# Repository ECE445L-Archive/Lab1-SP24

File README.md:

# ECE445L-Lab1

ECE445L Lab 1 Spring 2024.

IMPORTANT (for those not using Github Classroom): To clone this repository,
click the green "Use this template" button and create a PRIVATE repository. Do
NOT clone this repository as you would normally clone a git repo (i.e. using
'git clone ...') because you will not be able to make a private fork.

## HW

The hw folder should contain your schematic and board files for your PCB or
circuits. In later labs, you will be creating schematics for your circuit
in EAGLE. A setup tutorial can be found
[here](https://www.shawnvictor.net/autodesk-eagle.html).

## SW

The sw folder should contain your application firmware and software written for
the lab. The sw/inc folder contains firmware drivers written for you by
Professor Valvano. Feel free to write your own (in fact, in some labs, you may
be required to write your own).

You can place any other source files in the sw/ folder. TAs will look at the
files you create and/or modify for software quality and for running your
project.

## Resources

A couple files are provided in the Resources folder so you don't have to keep
searching for that one TI document. Some of them are immediately useful, like
the TM4C datasheet. Others may be useful for your final project, like the
TM4C_System_Design_Guidelines page.

## Git and Github

We will extensively use Git and Github for managing lab projects. This makes it
easier for TAs to grade and help debug the project by allowing the students to
see commit histories, maintain a common project structure, collaborate with
partners, merge different codebases, and to debug work.

Two common ways of using Git and Github are [Github Desktop](https://desktop.github.com/) and the [command line](https://git-scm.com/downloads). [Tutorials](https://dev.to/mollynem/git-github--workflow-fundamentals-5496) are also abundant on the net for you to peruse. We've provided a cheatsheet for git in the Resources folder.

It is highly recommended to make the most out of Git, even if you've never used
it before. Version control will save you a lot of suffering, and tools like Git
or SVN are ubiquitous in the industry.

## Lab Report

Following the lab doc provided at the root of this project, the TAs request you
submit a lab report in Microsoft Word (or Pages, if you're a Mac user). Please
name it `EID_lab_LAB_NUMBER_report.pdf`.

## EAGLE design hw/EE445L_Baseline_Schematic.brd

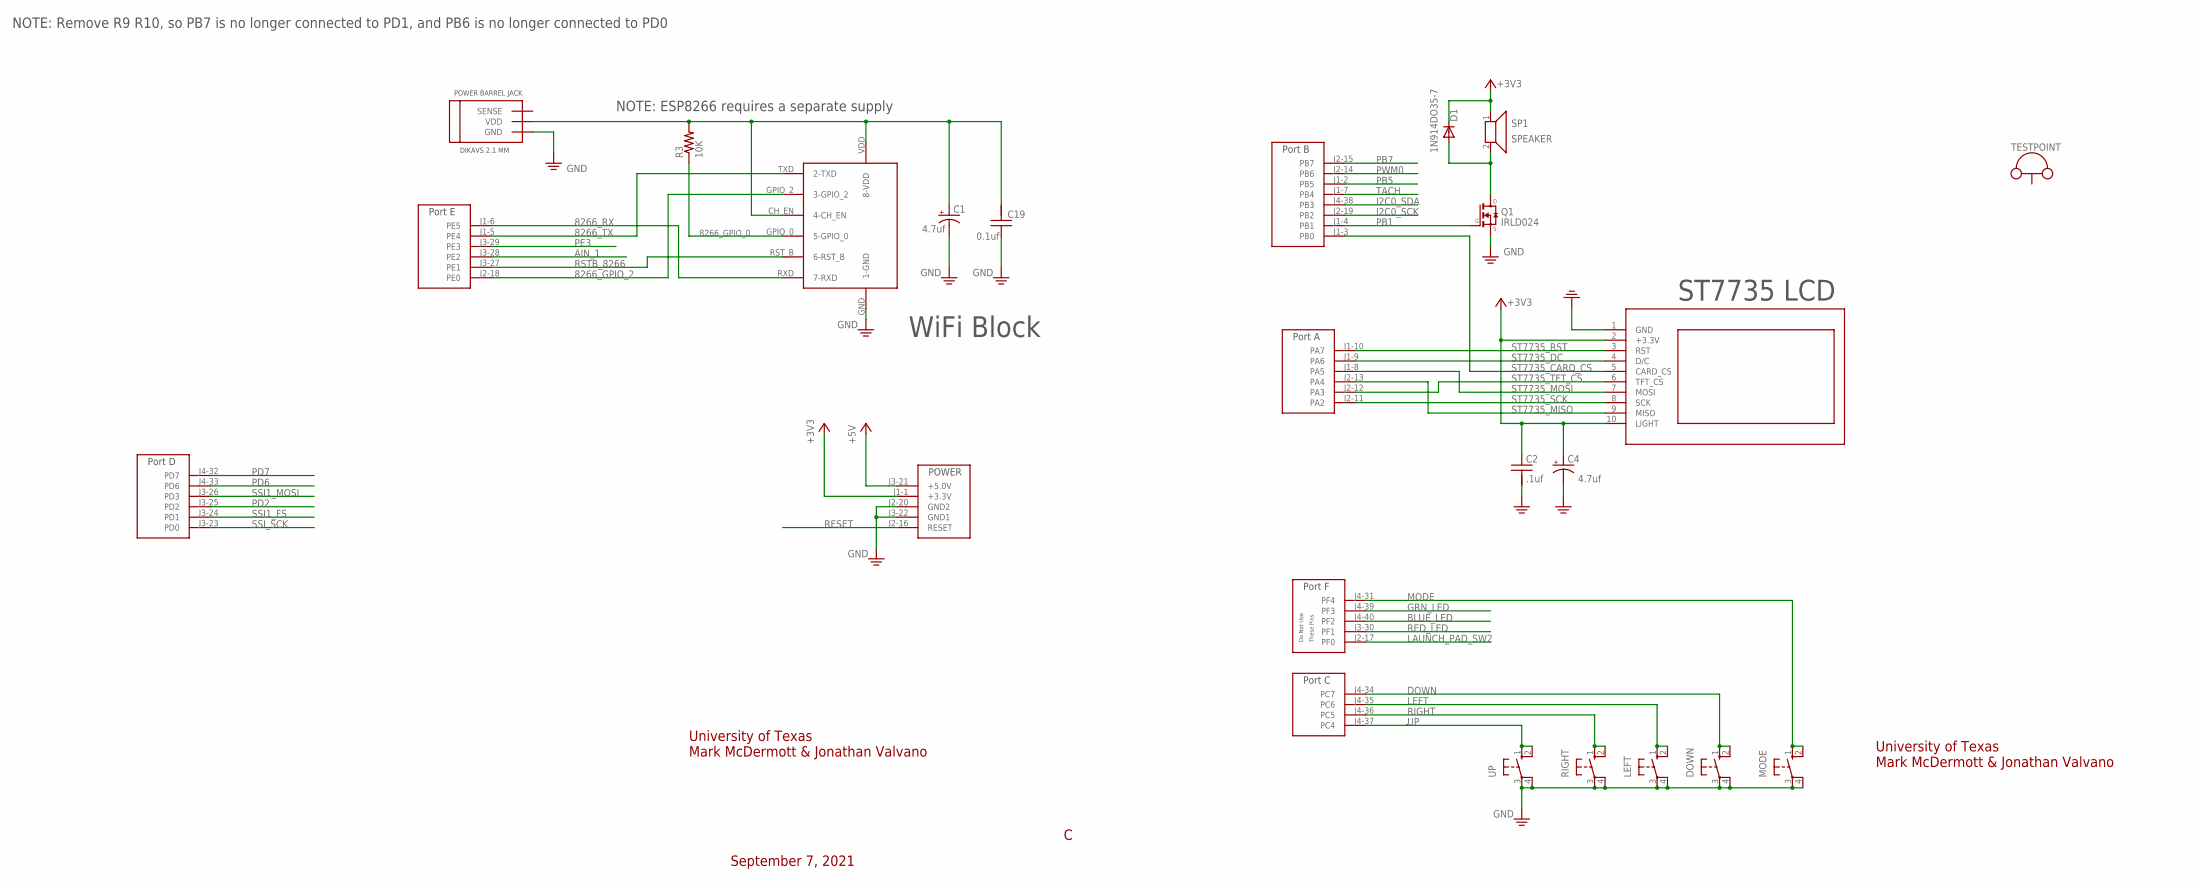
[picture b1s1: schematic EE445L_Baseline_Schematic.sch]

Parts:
C1, C4: 4.7uf; CAP200MILPOLARIZED
C2: .1uf; CAP200MIL
C19: 0.1uf; CAP200MIL
D1: 1N914DO35-7; DO35-7
DOWN: B3F-1052; B3F-10XX
LEFT: B3F-1052; B3F-10XX
MODE: B3F-1052; B3F-10XX
Q1: IRLD024
R3: 10K; RES300MIL
RIGHT: B3F-1052; B3F-10XX
SP1: SPEAKER; 1X02
TESTPOINT: TP_LOOP
U$1: ESP_8266; ESP8266
U$2: TM4C_BP; TM4C_BOOSTER_PACK
U$3: ST7735
U$4: 2.1MM_BARREL_JACK; 2.1M_BARREL_JACK
UP: B3F-1052; B3F-10XX

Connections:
8266_GPIO_0: R3.1, U$1.GPIO_0 (5-GPIO_0)
8266_GPIO_2: U$1.GPIO_2 (3-GPIO_2), U$2.J2-18 (PE0)
8266_RX: U$1.RXD (7-RXD), U$2.J1-6 (PE5)
8266_TX: U$1.TXD (2-TXD), U$2.J1-5 (PE4)
+3V3: C2.1, C4.+, D1.C, SP1.1, U$2.J1-1 (+3.3V), U$3.2 (+3.3V), U$3.10 (LIGHT)
+5V: U$2.J3-21 (+5.0V)
AIN_1: U$2.J3-28 (PE2)
BLUE_LED: U$2.J4-40 (PF2)
DOWN: DOWN.1 (S), DOWN.2 (S1), U$2.J4-34 (PC7)
GND: C1.-, C2.2, C4.-, C19.1, DOWN.3, DOWN.4 (P1), LEFT.3, LEFT.4 (P1), MODE.3, MODE.4 (P1), Q1.P$4 (S), RIGHT.3, RIGHT.4 (P1), U$1.GND (1-GND), U$2.J2-20 (GND2), U$2.J3-22 (GND1), U$3.1 (GND), U$4.GND, UP.3, UP.4 (P1)
GRN_LED: U$2.J4-39 (PF3)
I2C0_SCK: U$2.J2-19 (PB2)
I2C0_SDA: U$2.J4-38 (PB3)
LAUNCH_PAD_SW2: U$2.J2-17 (PF0)
LEFT: LEFT.1 (S), LEFT.2 (S1), U$2.J4-35 (PC6)
MODE: MODE.1 (S), MODE.2 (S1), U$2.J4-31 (PF4)
unnamed: D1.A, Q1.P$1 (D), SP1.2
unnamed: C1.+, C19.2, R3.2, U$1.CH_EN (4-CH_EN), U$1.VDD (8-VDD), U$4.VDD
PB1: Q1.P$3 (G), U$2.J1-4 (PB1)
PB5: U$2.J1-2 (PB5)
PB7: U$2.J2-15 (PB7)
PD2: U$2.J3-25 (PD2)
PD6: U$2.J4-33 (PD6)
PD7: U$2.J4-32 (PD7)
PE3: U$2.J3-29 (PE3)
PWM0: U$2.J2-14 (PB6)
RED_LED: U$2.J3-30 (PF1)
RESET: U$2.J2-16 (RESET)
RIGHT: RIGHT.1 (S), RIGHT.2 (S1), U$2.J4-36 (PC5)
RSTB_8266: U$1.RST_B (6-RST_B), U$2.J3-27 (PE1)
SSI1_FS: U$2.J3-24 (PD1)
SSI1_MOSI: U$2.J3-26 (PD3)
SSI_SCK: U$2.J3-23 (PD0)
ST7735_CARD_CS: U$2.J1-3 (PB0), U$3.5 (CARD_CS)
ST7735_DC: U$2.J1-9 (PA6), U$3.4 (D/C)
ST7735_MISO: U$2.J2-13 (PA4), U$3.9 (MISO)
ST7735_MOSI: U$2.J1-8 (PA5), U$3.7 (MOSI)
ST7735_RST: U$2.J1-10 (PA7), U$3.3 (RST)
ST7735_SCK: U$2.J2-11 (PA2), U$3.8 (SCK)
ST7735_TFT_CS: U$2.J2-12 (PA3), U$3.6 (TFT_CS)
TACH: U$2.J1-7 (PB4)
UP: U$2.J4-37 (PC4), UP.1 (S), UP.2 (S1)

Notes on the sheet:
WiFi Block
University of Texas Mark McDermott & Jonathan Valvano
September 7, 2021
ST7735 LCD
NOTE: ESP8266 requires a separate supply
NOTE: Remove R9 R10, so PB7 is no longer connected to PD1, and PB6 is no longer connected to PD0

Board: 2 copper layers, 18 parts (0 on the bottom side), 22 nets, no tracks yet.

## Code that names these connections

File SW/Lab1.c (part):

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 * @note Pinout:
 *    Backlight (pin 10) connected to +3.3 V
 *    MISO (pin 9) unconnected
 *    SCK (pin 8) connected to PA2 (SSI0Clk)
 *    MOSI (pin 7) connected to PA5 (SSI0Tx)
 *    TFT_CS (pin 6) connected to PA3 (SSI0Fss)
 *    CARD_CS (pin 5) unconnected
 *    Data/Command (pin 4) connected to PA6 (GPIO)
 *    RESET (pin 3) connected to PA7 (GPIO)
 *    VCC (pin 2) connected to +3.3 V
 *    Gnd (pin 1) connected to ground
 */
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/** MMAP Pin definitions. */
#define PF2   (*((volatile uint32_t *)0x40025010))
#define PF3   (*((volatile uint32_t *)0x40025020))
#define PF4   (*((volatile uint32_t *)0x40025040))


/** Function declarations. */
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void DelayWait10ms(uint32_t n);

/**
 * @brief PortF_Init initializes PF4 (Left Button <=> SW1) as an input and PF2
 *        (Blue onboard LED) as a digital output.
 * 
 */
void PortF_Init(void);

/**
 * @brief Blocks the current process until PF4 (Left Button <=> SW1) is pressed.
 */
void Pause(void);

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void PortF_Init(void) {
    SYSCTL_RCGCGPIO_R |= 0x20;          // 1) activate clock for Port F
    while((SYSCTL_PRGPIO_R&0x20)==0) {};// allow time for clock to start
                                        // 2) no need to unlock PF2, PF4
    GPIO_PORTF_PCTL_R &= ~0x000F0F00;   // 3) regular GPIO
    GPIO_PORTF_AMSEL_R &= ~0x14;        // 4) disable analog function on PF2, PF4
    GPIO_PORTF_PUR_R |= 0x10;           // 5) pullup for PF4
    GPIO_PORTF_DIR_R |= 0x04;           // 5) set direction to output
    GPIO_PORTF_AFSEL_R &= ~0x14;        // 6) regular port function
    GPIO_PORTF_DEN_R |= 0x14;           // 7) enable digital port
}

void Pause(void) {
    while(PF4==0x00) {
        DelayWait10ms(10);
    }
    while(PF4==0x10) {
        DelayWait10ms(10);
    }
}
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
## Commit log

2022-01-19 Starting point template. Lab1doc may be revised in the near future.
2022-01-24 update instructions for use
2022-08-24 Updated comments, function signatures, documentation, gitignore.
2022-08-29 Updated project options.
2022-08-30 clarified readme
2022-09-05 removed resolution red herring from ST7735 files
2022-10-09 file path changes.
2022-12-27 Update Lab01.docx
    Minor change to test process
2023-01-05 rename to lowercase
2023-01-05 remove uppercase folders
2023-01-10 rm hw folder for submodule replacement
2023-01-10 add hw folder as submodule
2023-01-10 rename inc in prep for submodule
2023-01-10 submodule include for inc folder
2023-01-10 removed old INC folder, added inc submodule changes
2023-01-10 moved src files to src folder, uploaded new lab01 doc
2023-01-12 make sure lab 1 compiles
2023-01-15 starter project files for using ccs
2023-01-15 get sw lib changes, targetconfigs for stellaris icdi ccs
2023-01-15 fix merge conflict
2023-01-26 updated lab1 change vers, uvprojx
2023-01-27 add in ccs .cmd layout file
2024-01-06 changed dates
2024-01-14 Lab1
    Lab 1 ready for review
2024-01-14 Stand alone project
    Temporary until I can figure GitHub
2024-01-15 Excluded autograder from gitignore; Fixed typo in include of PLL.h; Declared TrueR2 at beginning of for block, compatibility with CCS which doesnt have C99 enabled by default for TI compiler
2024-01-15 update incld rev
2024-01-22 Update Lab01Report.docx
    should have said main9, not main10

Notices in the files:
SW/Lab1.c:
@copyright Copyright (c) 2022
